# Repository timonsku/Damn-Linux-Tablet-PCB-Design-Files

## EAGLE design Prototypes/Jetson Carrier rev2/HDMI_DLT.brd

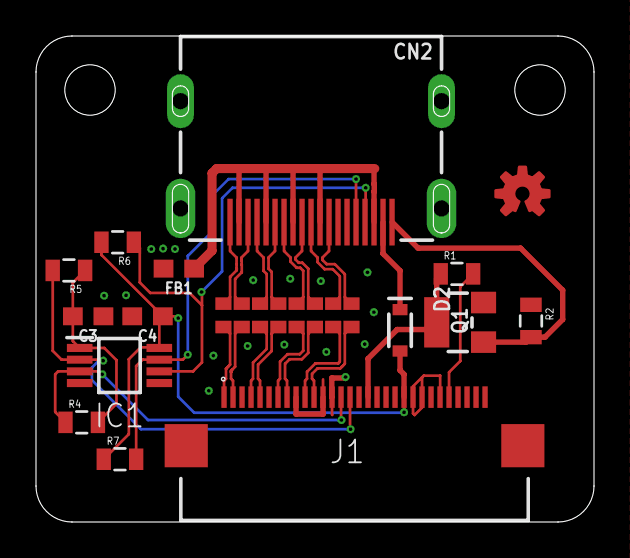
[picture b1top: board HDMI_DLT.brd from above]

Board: 4 copper layers, 31.0 x 27.0 mm, 23 parts (0 on the bottom side), 28 nets.

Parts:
C3, C4: 0.1uF; 0603
CN2: HDMI_MOLEX_47151-0001
D2: 1A/23V/620mV; SOD-323
FB1: .25/3A; 0603
IC1: PCA9517ADP,118; SOP65P490X110-8N
J1: 54132-3062
LOGO1: OSHW-LOGOS-COPPER; OSHW-LOGO-S_COPPER
Q1: SOT23-W
R1, R2: 4.7k; 0805
R3, R8, R9, R10, R11, R12, R13, R14: R0402
R4, R5, R6, R7: 10k; 0805

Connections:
1.8V: J1.26, R1.2
3.3V: C3.2, IC1.1, R4.2, R5.1
GND: C3.1, C4.2, CN2.P$1, CN2.P$2, CN2.P$3, CN2.P$4, FB1.2, IC1.4, J1.3, J1.6, J1.9, J1.12, J1.13, J1.18, J1.20, J1.22, J1.23, J1.25, J1.31, J1.32, Q1.2, R2.1
HDMI_5V_DIODE1: CN2.18, D2.C
HDMI_HPD: J1.17, Q1.3, R1.1
HDMI_HPD_IN: CN2.19, Q1.1, R2.2
HDMI_PWR_5V: C4.1, D2.A, IC1.8, J1.21, R6.2, R7.1
HDMI_SCL: IC1.2, J1.15, R5.2
HDMI_SCL_5V: CN2.15, IC1.7, R7.2
HDMI_SDA: IC1.3, J1.14, R4.1
HDMI_SDA_5V: CN2.16, IC1.6, R6.1
HDMI_SHIELD: CN2.2, CN2.5, CN2.8, CN2.11, CN2.17, FB1.1
TMDS_CLK_C1_N: CN2.12, R8.1
TMDS_CLK_C1_P: CN2.10, R3.1
TMDS_CLK_C_N: J1.11, R8.2
TMDS_CLK_C_P: J1.10, R3.2
TMDS_D0_C1_N: CN2.9, R10.1
TMDS_D0_C1_P: CN2.7, R9.1
TMDS_D0_C_N: J1.8, R10.2
TMDS_D0_C_P: J1.7, R9.2
TMDS_D1_C1_N: CN2.6, R12.1
TMDS_D1_C1_P: CN2.4, R11.1
TMDS_D1_C_N: J1.5, R12.2
TMDS_D1_C_P: J1.4, R11.2
TMDS_D2_C1_N: CN2.3, R14.1
TMDS_D2_C1_P: CN2.1, R13.1
TMDS_D2_C_N: J1.2, R14.2
TMDS_D2_C_P: J1.1, R13.2

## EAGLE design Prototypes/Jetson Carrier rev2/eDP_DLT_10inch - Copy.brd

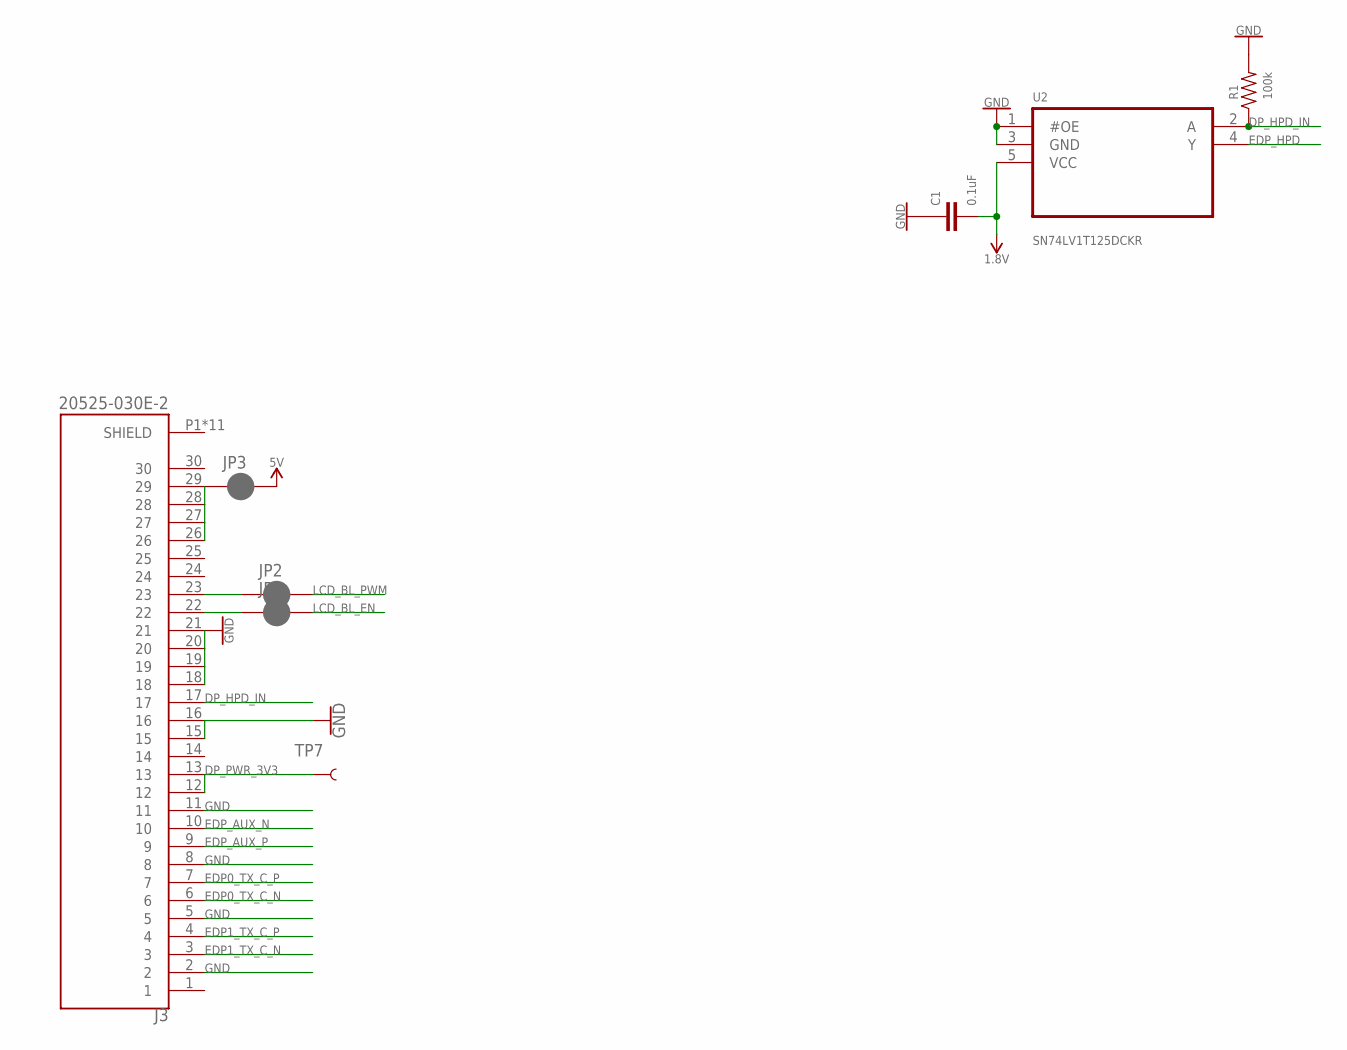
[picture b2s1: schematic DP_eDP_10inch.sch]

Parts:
C1: 0.1uF; 0603
J3: 20525-030E-2; I-PEX_20525-030E-2
JP1, JP2, JP3: JUMPER-SMT_2_NC_PASTE_NO-SILK; SMT-JUMPER_2_NC_PASTE_NO-SILK
R1: 100k; 0603-RES
TP7: TEST-POINT3; PAD.03X.03
U2: SN74LV1T125DCKR; SOT65P210X110-5N

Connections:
1.8V: C1.2, U2.5 (VCC); also elsewhere on the board
5V: JP3.2; also elsewhere on the board
DP_HPD_IN: J3.17, R1.1, U2.2 (A)
DP_PWR_3V3: J3.12, J3.13, TP7.P$1; also elsewhere on the board
EDP0_TX_C_N: J3.6; also elsewhere on the board
EDP0_TX_C_P: J3.7; also elsewhere on the board
EDP1_TX_C_N: J3.3; also elsewhere on the board
EDP1_TX_C_P: J3.4; also elsewhere on the board
EDP_AUX_N: J3.10; also elsewhere on the board
EDP_AUX_P: J3.9; also elsewhere on the board
EDP_HPD: U2.4 (Y); also elsewhere on the board
GND: C1.1, J3.2, J3.5, J3.8, J3.11, J3.15, J3.16, J3.18, J3.19, J3.20, J3.21, R1.2, U2.1 (#OE), U2.3 (GND); also elsewhere on the board
LCD_BL_EN: JP1.2; also elsewhere on the board
LCD_BL_PWM: JP2.2; also elsewhere on the board
unnamed: J3.22, JP1.1
unnamed: J3.23, JP2.1
unnamed: J3.26, J3.27, J3.28, J3.29, JP3.1

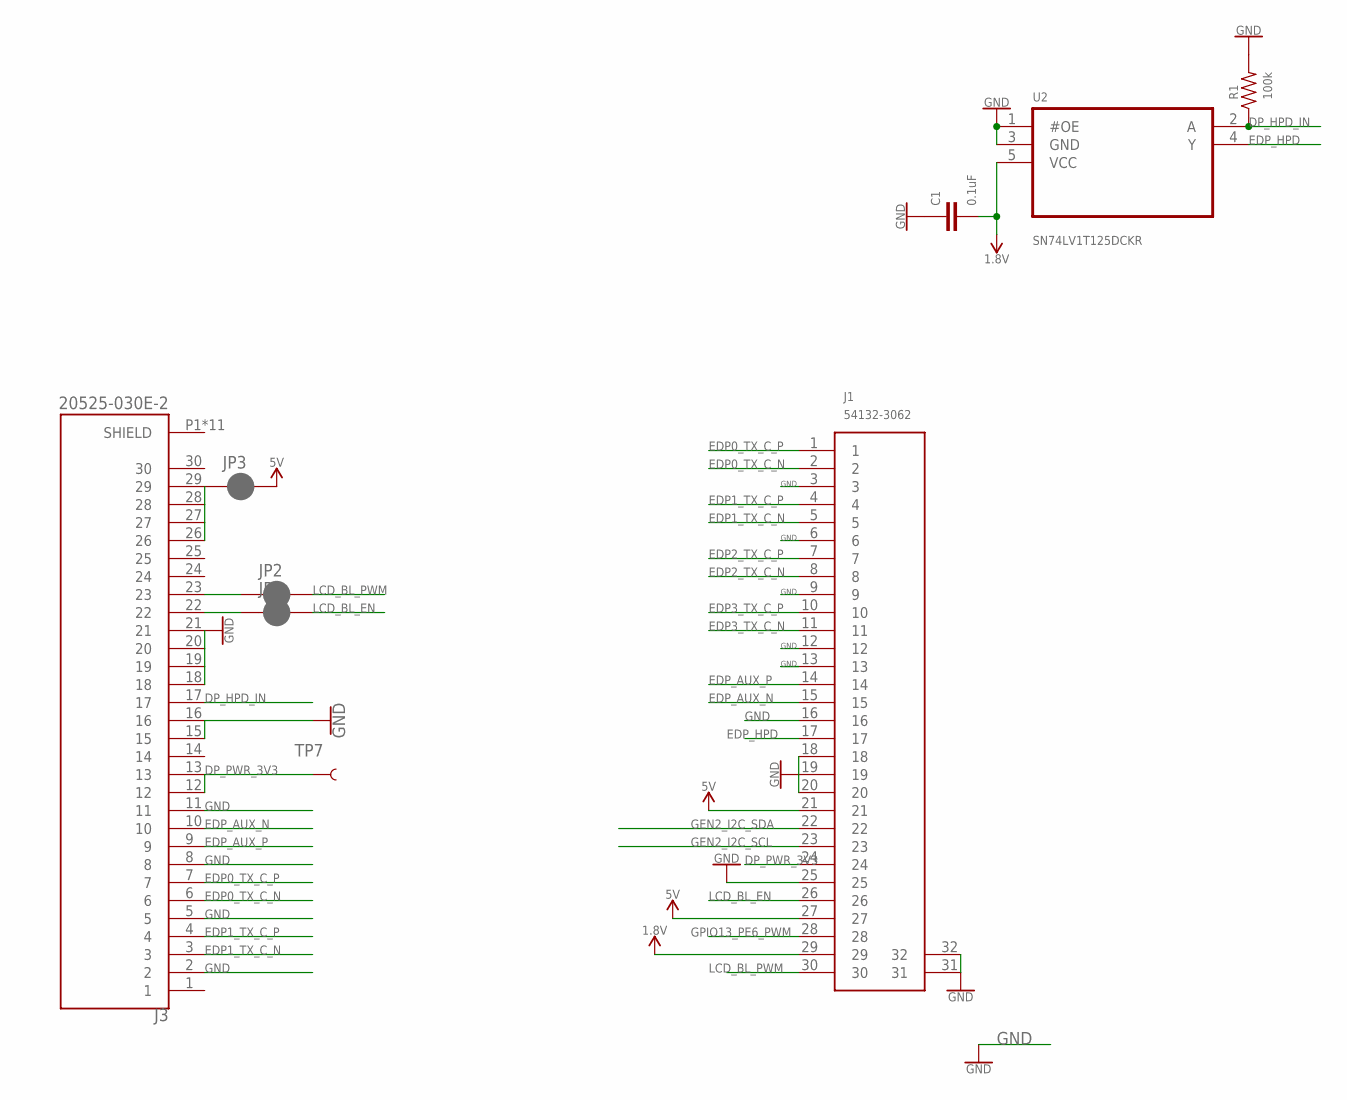
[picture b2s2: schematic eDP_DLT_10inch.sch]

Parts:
C1: 0.1uF; 0603
J1: 54132-3062
J3: 20525-030E-2; I-PEX_20525-030E-2
JP1, JP2, JP3: JUMPER-SMT_2_NC_PASTE_NO-SILK; SMT-JUMPER_2_NC_PASTE_NO-SILK
R1: 100k; 0603-RES
TP7: TEST-POINT3; PAD.03X.03
U2: SN74LV1T125DCKR; SOT65P210X110-5N

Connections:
1.8V: C1.2, J1.29, U2.5 (VCC)
5V: J1.21, J1.27, JP3.2
DP_HPD_IN: J3.17, R1.1, U2.2 (A)
DP_PWR_3V3: J1.24, J3.12, J3.13, TP7.P$1
EDP0_TX_C_N: J1.2, J3.6
EDP0_TX_C_P: J1.1, J3.7
EDP1_TX_C_N: J1.5, J3.3
EDP1_TX_C_P: J1.4, J3.4
EDP2_TX_C_N: J1.8
EDP2_TX_C_P: J1.7
EDP3_TX_C_N: J1.11
EDP3_TX_C_P: J1.10
EDP_AUX_N: J1.15, J3.10
EDP_AUX_P: J1.14, J3.9
EDP_HPD: J1.17, U2.4 (Y)
GEN2_I2C_SCL: J1.23
GEN2_I2C_SDA: J1.22
GND: C1.1, J1.3, J1.6, J1.9, J1.12, J1.13, J1.16, J1.18, J1.19, J1.20, J1.25, J1.31, J1.32, J3.2, J3.5, J3.8, J3.11, J3.15, J3.16, J3.18, J3.19, J3.20, J3.21, R1.2, U2.1 (#OE), U2.3 (GND)
GPIO13_PE6_PWM: J1.28
LCD_BL_EN: J1.26, JP1.2
LCD_BL_PWM: J1.30, JP2.2
unnamed: J3.22, JP1.1
unnamed: J3.23, JP2.1
unnamed: J3.26, J3.27, J3.28, J3.29, JP3.1

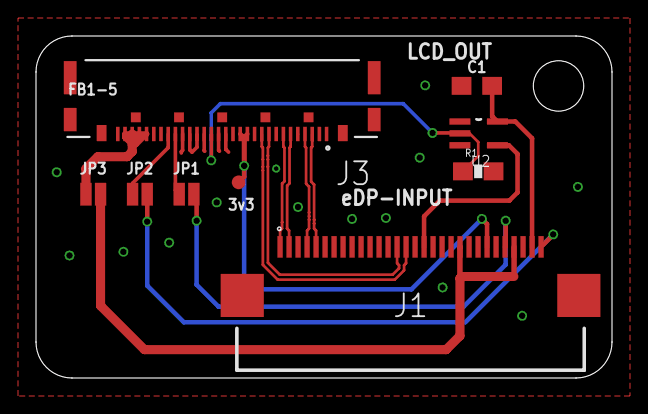
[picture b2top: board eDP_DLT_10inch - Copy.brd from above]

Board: 4 copper layers, 32.0 x 19.0 mm, 9 parts (0 on the bottom side), 17 nets.

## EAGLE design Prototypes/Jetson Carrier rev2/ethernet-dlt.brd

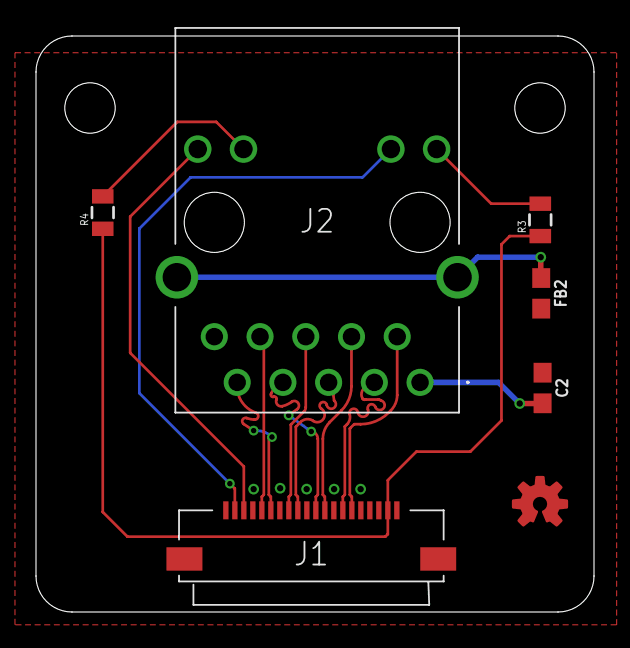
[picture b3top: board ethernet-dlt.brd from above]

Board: 4 copper layers, 31.0 x 32.0 mm, 7 parts (0 on the bottom side), 16 nets.

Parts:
C2: 10nF; 0603
FB2: .25/3A; 0603
J1: 505110-2091; 5051102091
J2: 93626-3508; 936263508
LOGO1: OSHW-LOGOS-COPPER; OSHW-LOGO-S_COPPER
R3, R4: 220; 0805

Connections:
3.3V: J1.19, R3.1, R4.1
ENET_LED0: J1.3, J2.14
ENET_LED1: J1.2, J2.12
ENET_TRD0_N: J1.14, J2.3
ENET_TRD0_P: J1.15, J2.2
ENET_TRD1_N: J1.11, J2.7
ENET_TRD1_P: J1.12, J2.4
ENET_TRD2_N: J1.8, J2.6
ENET_TRD2_P: J1.9, J2.5
ENET_TRD3_N: J1.6, J2.9
ENET_TRD3_P: J1.5, J2.8
GND: C2.1, FB2.2, J1.4, J1.7, J1.10, J1.13, J1.16, J1.MP1, J1.MP2, J2.10
unnamed: J2.11, R3.2
unnamed: J2.13, R4.2
unnamed: C2.2, J2.1
unnamed: FB2.1, J2.MH1, J2.MH2

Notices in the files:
parts and their libraries:
SparkFun-PowerSymbols: Licensing: Creative Commons ShareAlike 4.0 International - https://creativecommons.org/licenses/by-sa/4.0
microbuilder: This work is placed in the public domain, and may be freely used for commercial and non-commercial work with the following conditions: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
